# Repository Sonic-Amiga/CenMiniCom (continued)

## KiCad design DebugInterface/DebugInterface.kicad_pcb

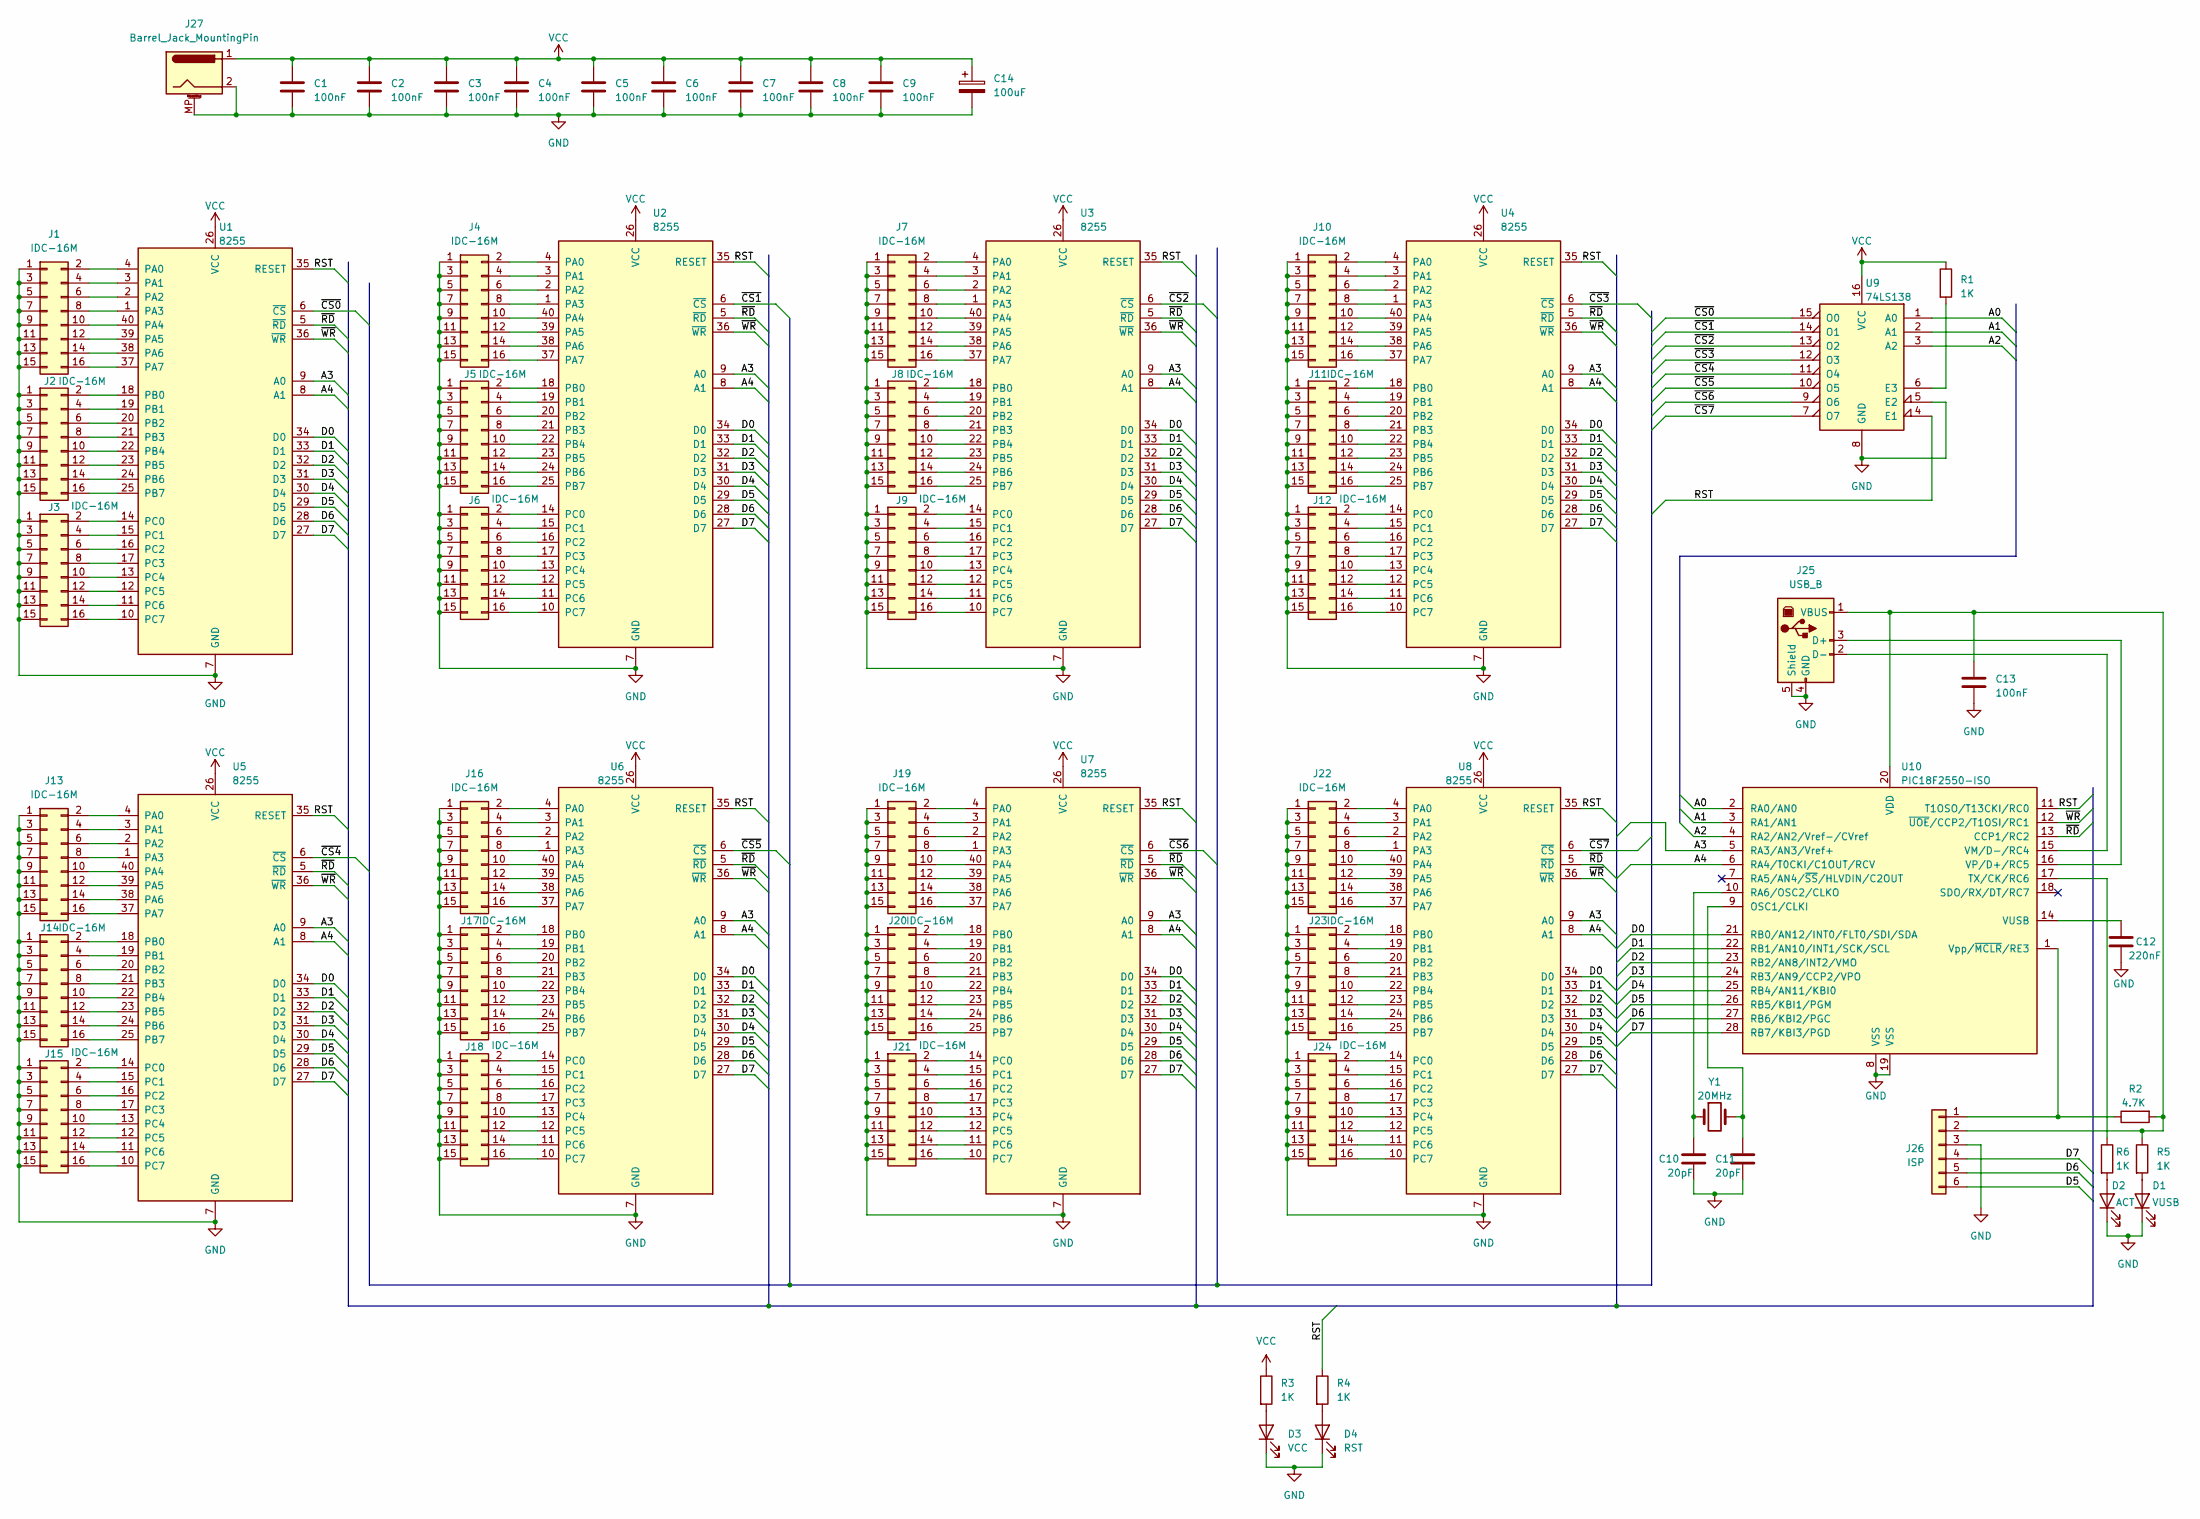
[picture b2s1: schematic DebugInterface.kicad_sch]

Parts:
C1, C2, C3, C4, C5, C6, C7, C8, C9, C13: 100nF; C_Disc_D4.3mm_W1.9mm_P5.00mm
C10, C11: 20pF; C_Disc_D4.3mm_W1.9mm_P5.00mm
C12: 220nF; C_Disc_D4.3mm_W1.9mm_P5.00mm
C14: 100uF; CP_Radial_D8.0mm_P3.80mm
D1: VUSB; LED_D3.0mm
D2: ACT; LED_D3.0mm
D3: VCC; LED_D3.0mm
D4: RST; LED_D3.0mm
J1, J2, J3, J4, J5, J6, J7, J8, J9, J10, J11, J12, J13, J14, J15, J16, J17, J18, J19, J20, J21, J22, J23, J24: IDC-16M; IDC-Header_2x08_P2.54mm_Vertical
J25: USB_B; USB_B_OST_USB-B1HSxx_Horizontal
J26: ISP; PinHeader_1x06_P2.54mm_Vertical
J27: Barrel_Jack_MountingPin; BarrelJack_GCT_DCJ200-10-A_Horizontal
R1, R3, R4, R5, R6: 1K; R_Axial_DIN0207_L6.3mm_D2.5mm_P10.16mm_Horizontal
R2: 4.7K; R_Axial_DIN0207_L6.3mm_D2.5mm_P10.16mm_Horizontal
U1, U2, U3, U4, U5, U6, U7, U8: 8255; DIP-40_W15.24mm
U9: 74LS138; DIP-16_W7.62mm
U10: PIC18F2550-ISO; SOIC-28W_7.5x17.9mm_P1.27mm
Y1: 20MHz; Crystal_HC49-U_Vertical

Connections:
/A0: U9.1 (A0), U10.2 (RA0/AN0)
/A1: U9.2 (A1), U10.3 (RA1/AN1)
/A2: U9.3 (A2), U10.4 (RA2/AN2/Vref-/CVref)
/A3: U1.9 (A0), U2.9 (A0), U3.9 (A0), U4.9 (A0), U5.9 (A0), U6.9 (A0), U7.9 (A0), U8.9 (A0), U10.5 (RA3/AN3/Vref+)
/A4: U1.8 (A1), U2.8 (A1), U3.8 (A1), U4.8 (A1), U5.8 (A1), U6.8 (A1), U7.8 (A1), U8.8 (A1), U10.6 (RA4/T0CKI/C1OUT/RCV)
/D0: U1.34 (D0), U2.34 (D0), U3.34 (D0), U4.34 (D0), U5.34 (D0), U6.34 (D0), U7.34 (D0), U8.34 (D0), U10.21 (RB0/AN12/INT0/FLT0/SDI/SDA)
/D1: U1.33 (D1), U2.33 (D1), U3.33 (D1), U4.33 (D1), U5.33 (D1), U6.33 (D1), U7.33 (D1), U8.33 (D1), U10.22 (RB1/AN10/INT1/SCK/SCL)
/D2: U1.32 (D2), U2.32 (D2), U3.32 (D2), U4.32 (D2), U5.32 (D2), U6.32 (D2), U7.32 (D2), U8.32 (D2), U10.23 (RB2/AN8/INT2/VMO)
/D3: U1.31 (D3), U2.31 (D3), U3.31 (D3), U4.31 (D3), U5.31 (D3), U6.31 (D3), U7.31 (D3), U8.31 (D3), U10.24 (RB3/AN9/CCP2/VPO)
/D4: U1.30 (D4), U2.30 (D4), U3.30 (D4), U4.30 (D4), U5.30 (D4), U6.30 (D4), U7.30 (D4), U8.30 (D4), U10.25 (RB4/AN11/KBI0)
/D5: J26.6, U1.29 (D5), U2.29 (D5), U3.29 (D5), U4.29 (D5), U5.29 (D5), U6.29 (D5), U7.29 (D5), U8.29 (D5), U10.26 (RB5/KBI1/PGM)
/D6: J26.5, U1.28 (D6), U2.28 (D6), U3.28 (D6), U4.28 (D6), U5.28 (D6), U6.28 (D6), U7.28 (D6), U8.28 (D6), U10.27 (RB6/KBI2/PGC)
/D7: J26.4, U1.27 (D7), U2.27 (D7), U3.27 (D7), U4.27 (D7), U5.27 (D7), U6.27 (D7), U7.27 (D7), U8.27 (D7), U10.28 (RB7/KBI3/PGD)
/RST: R4.1, U1.35 (RESET), U2.35 (RESET), U3.35 (RESET), U4.35 (RESET), U5.35 (RESET), U6.35 (RESET), U7.35 (RESET), U8.35 (RESET), U9.4 (E1), U10.11 (T1OSO/T13CKI/RC0)
/~CS0: U1.6 (~CS), U9.15 (O0)
/~CS1: U2.6 (~CS), U9.14 (O1)
/~CS2: U3.6 (~CS), U9.13 (O2)
/~CS3: U4.6 (~CS), U9.12 (O3)
/~CS4: U5.6 (~CS), U9.11 (O4)
/~CS5: U6.6 (~CS), U9.10 (O5)
/~CS6: U7.6 (~CS), U9.9 (O6)
/~CS7: U8.6 (~CS), U9.7 (O7)
/~RD: U1.5 (~RD), U2.5 (~RD), U3.5 (~RD), U4.5 (~RD), U5.5 (~RD), U6.5 (~RD), U7.5 (~RD), U8.5 (~RD), U10.13 (CCP1/RC2)
/~WR: U1.36 (~WR), U2.36 (~WR), U3.36 (~WR), U4.36 (~WR), U5.36 (~WR), U6.36 (~WR), U7.36 (~WR), U8.36 (~WR), U10.12 (~UOE/CCP2/T1OSI/RC1)
GND: C1.2, C2.2, C3.2, C4.2, C5.2, C6.2, C7.2, C8.2, C9.2, C10.1, C11.1, C12.2, C13.2, C14.2, D1.1 (K), D2.1 (K), D3.1 (K), D4.1 (K), J1.1, J1.3, J1.5, J1.7, J1.9, J1.11, J1.13, J1.15, J2.1, J2.3, J2.5, J2.7, J2.9, J2.11, J2.13, J2.15, J3.1, J3.3, J3.5, J3.7, J3.9, J3.11, J3.13, J3.15, J4.1, J4.3, J4.5, J4.7, J4.9, J4.11, J4.13, J4.15, J5.1, J5.3, J5.5, J5.7, J5.9, J5.11, J5.13, J5.15, J6.1, J6.3, J6.5, J6.7, J6.9, J6.11, J6.13, J6.15, J7.1, J7.3, J7.5, J7.7, J7.9, J7.11, J7.13, J7.15, J8.1, J8.3, J8.5, J8.7, J8.9, J8.11, J8.13, J8.15, J9.1, J9.3, J9.5, J9.7, J9.9, J9.11, J9.13, J9.15, J10.1, J10.3, J10.5, J10.7, J10.9, J10.11, J10.13, J10.15, J11.1, J11.3, J11.5, J11.7, J11.9, J11.11, J11.13, J11.15, J12.1, J12.3, J12.5, J12.7, J12.9, J12.11, J12.13, J12.15, J13.1, J13.3, J13.5, J13.7, J13.9, J13.11, J13.13, J13.15, J14.1, J14.3, J14.5, J14.7, J14.9, J14.11, J14.13, J14.15, J15.1, J15.3, J15.5, J15.7, J15.9, J15.11, J15.13, J15.15, J16.1, J16.3, J16.5, J16.7, J16.9, J16.11, J16.13, J16.15, J17.1, J17.3, J17.5, J17.7, J17.9, J17.11, J17.13, J17.15, J18.1, J18.3, J18.5, J18.7, J18.9, J18.11, J18.13, J18.15, J19.1, J19.3, J19.5, J19.7, J19.9, J19.11, J19.13, J19.15, J20.1, J20.3, J20.5, J20.7, J20.9, J20.11, J20.13, J20.15, J21.1, J21.3, J21.5, J21.7, J21.9, J21.11, J21.13, J21.15, J22.1, J22.3, J22.5, J22.7, J22.9, J22.11, J22.13, J22.15, J23.1, J23.3, J23.5, J23.7, J23.9, J23.11, J23.13, J23.15, J24.1, J24.3, J24.5, J24.7, J24.9, J24.11, J24.13, J24.15, J25.4 (GND), J25.5 (Shield), J26.3, J27.2, J27.MP (MountPin), U1.7 (GND), U2.7 (GND), U3.7 (GND), U4.7 (GND), U5.7 (GND), U6.7 (GND), U7.7 (GND), U8.7 (GND), U9.5 (E2), U9.8 (GND), U10.8 (VSS), U10.19 (VSS)
unnamed: D1.2 (A), R5.2
unnamed: D2.2 (A), R6.2
unnamed: D3.2 (A), R3.2
unnamed: D4.2 (A), R4.2
unnamed: J1.2, U1.4 (PA0)
unnamed: J1.4, U1.3 (PA1)
unnamed: J1.6, U1.2 (PA2)
unnamed: J1.8, U1.1 (PA3)
unnamed: J1.10, U1.40 (PA4)
unnamed: J1.12, U1.39 (PA5)
unnamed: J1.14, U1.38 (PA6)
unnamed: J1.16, U1.37 (PA7)
unnamed: J2.2, U1.18 (PB0)
unnamed: J2.4, U1.19 (PB1)
unnamed: J2.6, U1.20 (PB2)
unnamed: J2.8, U1.21 (PB3)
unnamed: J2.10, U1.22 (PB4)
unnamed: J2.12, U1.23 (PB5)
unnamed: J2.14, U1.24 (PB6)
unnamed: J2.16, U1.25 (PB7)
unnamed: J3.2, U1.14 (PC0)
unnamed: J3.4, U1.15 (PC1)
unnamed: J3.6, U1.16 (PC2)
unnamed: J3.8, U1.17 (PC3)
unnamed: J3.10, U1.13 (PC4)
unnamed: J3.12, U1.12 (PC5)
unnamed: J3.14, U1.11 (PC6)
unnamed: J3.16, U1.10 (PC7)
unnamed: J4.2, U2.4 (PA0)
unnamed: J4.4, U2.3 (PA1)
unnamed: J4.6, U2.2 (PA2)
unnamed: J4.8, U2.1 (PA3)
unnamed: J4.10, U2.40 (PA4)
unnamed: J4.12, U2.39 (PA5)
unnamed: J4.14, U2.38 (PA6)
unnamed: J4.16, U2.37 (PA7)
unnamed: J5.2, U2.18 (PB0)
unnamed: J5.4, U2.19 (PB1)
unnamed: J5.6, U2.20 (PB2)
unnamed: J5.8, U2.21 (PB3)
unnamed: J5.10, U2.22 (PB4)
unnamed: J5.12, U2.23 (PB5)
unnamed: J5.14, U2.24 (PB6)
unnamed: J5.16, U2.25 (PB7)
unnamed: J6.2, U2.14 (PC0)
unnamed: J6.4, U2.15 (PC1)
unnamed: J6.6, U2.16 (PC2)
unnamed: J6.8, U2.17 (PC3)
unnamed: J6.10, U2.13 (PC4)
unnamed: J6.12, U2.12 (PC5)
unnamed: J6.14, U2.11 (PC6)
unnamed: J6.16, U2.10 (PC7)
unnamed: J7.2, U3.4 (PA0)
unnamed: J7.4, U3.3 (PA1)
unnamed: J7.6, U3.2 (PA2)
unnamed: J7.8, U3.1 (PA3)
unnamed: J7.10, U3.40 (PA4)
unnamed: J7.12, U3.39 (PA5)
unnamed: J7.14, U3.38 (PA6)
unnamed: J7.16, U3.37 (PA7)
unnamed: J8.2, U3.18 (PB0)
unnamed: J8.4, U3.19 (PB1)
unnamed: J8.6, U3.20 (PB2)
unnamed: J8.8, U3.21 (PB3)
unnamed: J8.10, U3.22 (PB4)
unnamed: J8.12, U3.23 (PB5)
unnamed: J8.14, U3.24 (PB6)
unnamed: J8.16, U3.25 (PB7)
unnamed: J9.2, U3.14 (PC0)
unnamed: J9.4, U3.15 (PC1)
unnamed: J9.6, U3.16 (PC2)
unnamed: J9.8, U3.17 (PC3)
unnamed: J9.10, U3.13 (PC4)
unnamed: J9.12, U3.12 (PC5)
unnamed: J9.14, U3.11 (PC6)
unnamed: J9.16, U3.10 (PC7)
unnamed: J10.2, U4.4 (PA0)
unnamed: J10.4, U4.3 (PA1)
unnamed: J10.6, U4.2 (PA2)
unnamed: J10.8, U4.1 (PA3)
unnamed: J10.10, U4.40 (PA4)
unnamed: J10.12, U4.39 (PA5)
unnamed: J10.14, U4.38 (PA6)
unnamed: J10.16, U4.37 (PA7)
unnamed: J11.2, U4.18 (PB0)
unnamed: J11.4, U4.19 (PB1)
unnamed: J11.6, U4.20 (PB2)
unnamed: J11.8, U4.21 (PB3)
unnamed: J11.10, U4.22 (PB4)
unnamed: J11.12, U4.23 (PB5)
unnamed: J11.14, U4.24 (PB6)
unnamed: J11.16, U4.25 (PB7)
unnamed: J12.2, U4.14 (PC0)
unnamed: J12.4, U4.15 (PC1)
unnamed: J12.6, U4.16 (PC2)
unnamed: J12.8, U4.17 (PC3)
unnamed: J12.10, U4.13 (PC4)
unnamed: J12.12, U4.12 (PC5)
unnamed: J12.14, U4.11 (PC6)
unnamed: J12.16, U4.10 (PC7)
unnamed: J13.2, U5.4 (PA0)
unnamed: J13.4, U5.3 (PA1)
unnamed: J13.6, U5.2 (PA2)
unnamed: J13.8, U5.1 (PA3)
unnamed: J13.10, U5.40 (PA4)
unnamed: J13.12, U5.39 (PA5)
unnamed: J13.14, U5.38 (PA6)
unnamed: J13.16, U5.37 (PA7)
unnamed: J14.2, U5.18 (PB0)
unnamed: J14.4, U5.19 (PB1)
unnamed: J14.6, U5.20 (PB2)
unnamed: J14.8, U5.21 (PB3)
unnamed: J14.10, U5.22 (PB4)
unnamed: J14.12, U5.23 (PB5)
unnamed: J14.14, U5.24 (PB6)
unnamed: J14.16, U5.25 (PB7)
unnamed: J15.2, U5.14 (PC0)
unnamed: J15.4, U5.15 (PC1)
unnamed: J15.6, U5.16 (PC2)
unnamed: J15.8, U5.17 (PC3)
unnamed: J15.10, U5.13 (PC4)
unnamed: J15.12, U5.12 (PC5)
unnamed: J15.14, U5.11 (PC6)
unnamed: J15.16, U5.10 (PC7)
unnamed: J16.2, U6.4 (PA0)
unnamed: J16.4, U6.3 (PA1)
unnamed: J16.6, U6.2 (PA2)
unnamed: J16.8, U6.1 (PA3)
unnamed: J16.10, U6.40 (PA4)
unnamed: J16.12, U6.39 (PA5)
unnamed: J16.14, U6.38 (PA6)
unnamed: J16.16, U6.37 (PA7)
unnamed: J17.2, U6.18 (PB0)
unnamed: J17.4, U6.19 (PB1)
unnamed: J17.6, U6.20 (PB2)
unnamed: J17.8, U6.21 (PB3)
unnamed: J17.10, U6.22 (PB4)
unnamed: J17.12, U6.23 (PB5)
unnamed: J17.14, U6.24 (PB6)
unnamed: J17.16, U6.25 (PB7)
unnamed: J18.2, U6.14 (PC0)
unnamed: J18.4, U6.15 (PC1)
unnamed: J18.6, U6.16 (PC2)
unnamed: J18.8, U6.17 (PC3)
unnamed: J18.10, U6.13 (PC4)
unnamed: J18.12, U6.12 (PC5)
unnamed: J18.14, U6.11 (PC6)
unnamed: J18.16, U6.10 (PC7)
unnamed: J19.2, U7.4 (PA0)
unnamed: J19.4, U7.3 (PA1)
unnamed: J19.6, U7.2 (PA2)
unnamed: J19.8, U7.1 (PA3)
unnamed: J19.10, U7.40 (PA4)
unnamed: J19.12, U7.39 (PA5)
unnamed: J19.14, U7.38 (PA6)
unnamed: J19.16, U7.37 (PA7)
unnamed: J20.2, U7.18 (PB0)
unnamed: J20.4, U7.19 (PB1)
unnamed: J20.6, U7.20 (PB2)
unnamed: J20.8, U7.21 (PB3)
unnamed: J20.10, U7.22 (PB4)
unnamed: J20.12, U7.23 (PB5)
unnamed: J20.14, U7.24 (PB6)
unnamed: J20.16, U7.25 (PB7)
unnamed: J21.2, U7.14 (PC0)
unnamed: J21.4, U7.15 (PC1)
unnamed: J21.6, U7.16 (PC2)
unnamed: J21.8, U7.17 (PC3)
unnamed: J21.10, U7.13 (PC4)
unnamed: J21.12, U7.12 (PC5)
unnamed: J21.14, U7.11 (PC6)
unnamed: J21.16, U7.10 (PC7)
unnamed: J22.2, U8.4 (PA0)
unnamed: J22.4, U8.3 (PA1)
unnamed: J22.6, U8.2 (PA2)
unnamed: J22.8, U8.1 (PA3)
unnamed: J22.10, U8.40 (PA4)
unnamed: J22.12, U8.39 (PA5)
unnamed: J22.14, U8.38 (PA6)
unnamed: J22.16, U8.37 (PA7)
unnamed: J23.2, U8.18 (PB0)
unnamed: J23.4, U8.19 (PB1)
unnamed: J23.6, U8.20 (PB2)
unnamed: J23.8, U8.21 (PB3)
unnamed: J23.10, U8.22 (PB4)
unnamed: J23.12, U8.23 (PB5)
unnamed: J23.14, U8.24 (PB6)
unnamed: J23.16, U8.25 (PB7)
unnamed: J24.2, U8.14 (PC0)
unnamed: J24.4, U8.15 (PC1)
unnamed: J24.6, U8.16 (PC2)
unnamed: J24.8, U8.17 (PC3)
unnamed: J24.10, U8.13 (PC4)
unnamed: J24.12, U8.12 (PC5)
unnamed: J24.14, U8.11 (PC6)
unnamed: J24.16, U8.10 (PC7)
unnamed: J25.3 (D+), U10.16 (VP/D+/RC5)
unnamed: J25.2 (D-), U10.15 (VM/D-/RC4)
unnamed: C13.1, J25.1 (VBUS), J26.2, R2.2, R5.1, U10.20 (VDD)
unnamed: J26.1, R2.1, U10.1 (Vpp/~MCLR/RE3)
unnamed: R1.2, U9.6 (E3)
unnamed: C11.2, U10.9 (OSC1/CLKI), Y1.2
unnamed: C10.2, U10.10 (RA6/OSC2/CLKO), Y1.1
unnamed: R6.1, U10.17 (TX/CK/RC6)
unnamed: C12.1, U10.14 (VUSB)
VCC: C1.1, C2.1, C3.1, C4.1, C5.1, C6.1, C7.1, C8.1, C9.1, C14.1, J27.1, R1.1, R3.1, U1.26 (VCC), U2.26 (VCC), U3.26 (VCC), U4.26 (VCC), U5.26 (VCC), U6.26 (VCC), U7.26 (VCC), U8.26 (VCC), U9.16 (VCC)

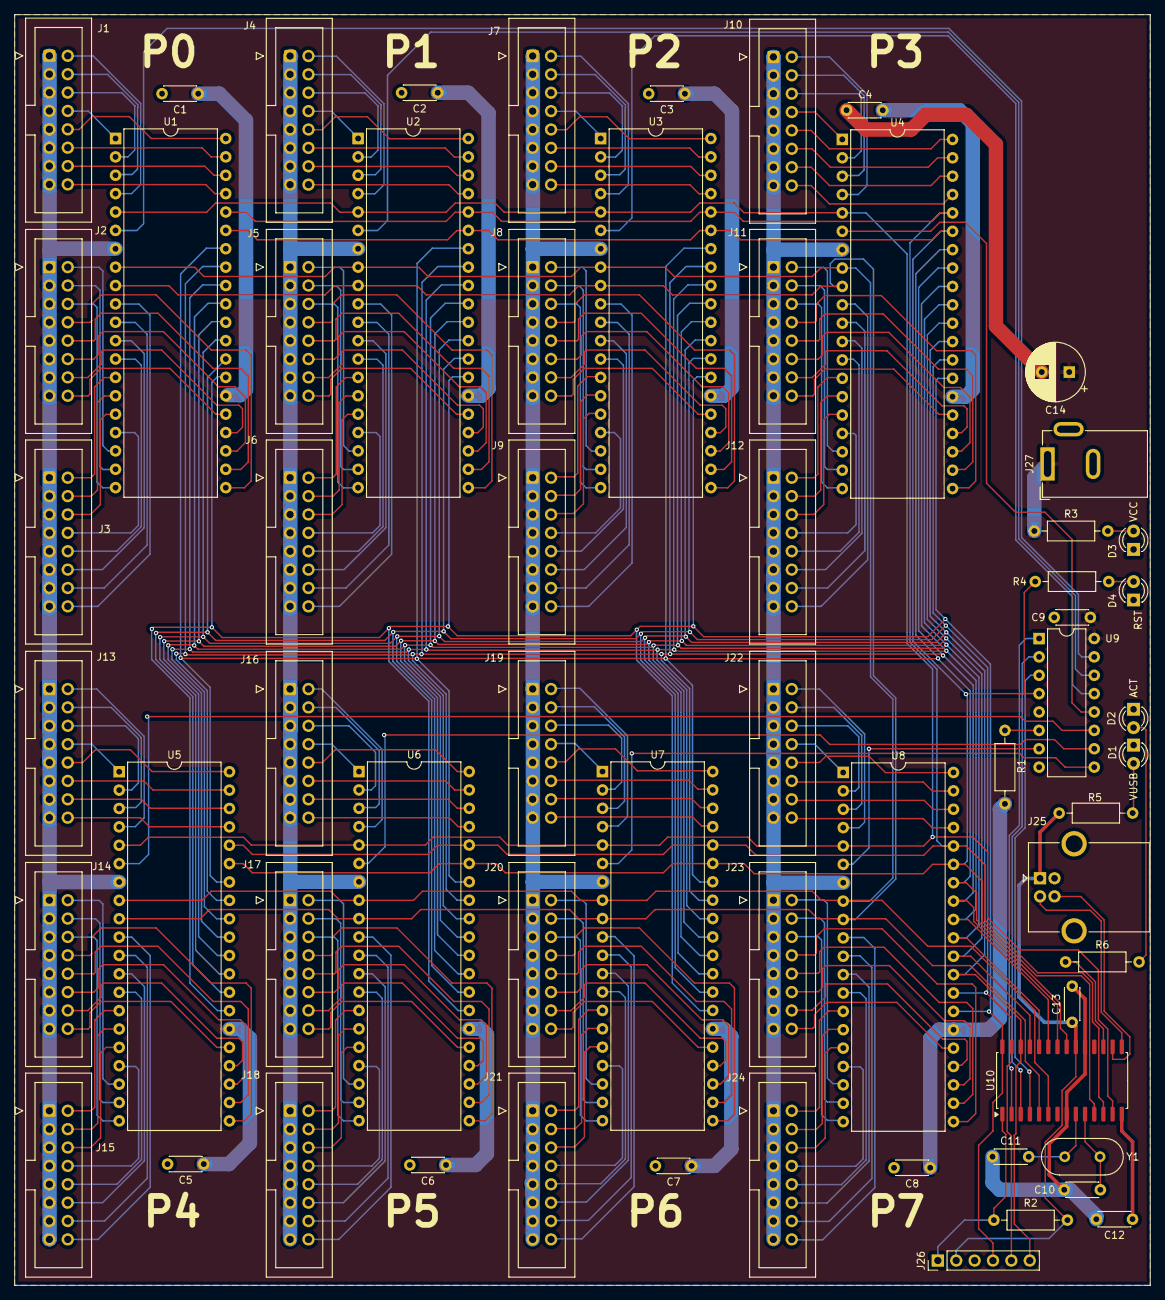
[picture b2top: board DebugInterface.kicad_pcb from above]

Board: 2 copper layers, 157.0 x 175.6 mm, 62 parts (0 on the bottom side), 231 nets.

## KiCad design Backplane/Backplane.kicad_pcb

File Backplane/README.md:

# Backplane board replica

# Modifications list.

1. TBP18S42N ROM is a complete ubobtanium, so i found a russian КР556РТ5 (KR556RT5)
one-time fuse ROM. A cross-reference site gave "3605" as a western analog for the
chip, so let it be so.

2. PCB-mounted edge slots are also a complete unobtanium here, i only found ones for
soldering wires, they are called SLM-72:
https://www.arcadepartsandrepair.com/store/pinball-kits-parts/pinball-parts/72-pin-edge-connector-w-solder-eyelet-leads-ec1007/
Therefore this PCB is a shortened version, only containing boot ROM and LED buffers, but
the design is modular and can be extended, see assembly notes.
Connection to the bus is made using a 50-pin connector, you may use IDC type with a flat
ribbon cable. 
If you have access to the PCB-mounted connectors, please feel free to extend the project.
I will be happy to host the full version in the repository.

3. Real-time clock reference generator has been omitted. Modern PSUs don't output any low
voltage AC, and it's much easier to just generate the frequency needed. Since the signal
comes into the CPU from front panel side, front panel board takes care of it.

Russian characters in this file are using UTF-8 character set.

# Assembly notes

Possible chip replacements:

|Original       |Replacement            |
|---------------|-----------------------|
|3604		|К556РТ5		|
|7425		|155ЛЕ3			|
|74LS04         |К555ЛН1		|
|74LS20		|К555ЛА1		|
|74LS38		|К555ЛА13		|

As noticed above, this backplane design is modular, and can be used with both wired and PCB backplane
design. For the purpose, the J2 connector is designed as a horisontal 2x25 pins row. It is possible
to attach a second board, containing edge slots, directly to it, thus producing a full-sized backplane.
Alternatively, an IDC-50 connector can be installed with a flat ribbon cable, going to a wired backplane
(this will be my implementation). Sorry, due to a lack of time i don't have a design for the second PCB,
but i would be happy if someone contributes.

# Revision history.

28.11.2022 - rev 1.0

* Erratum E001: Incorrect DIP chip width is used for 3604

# Contacts

Please direct all questions to pavel_fedin@mail.ru

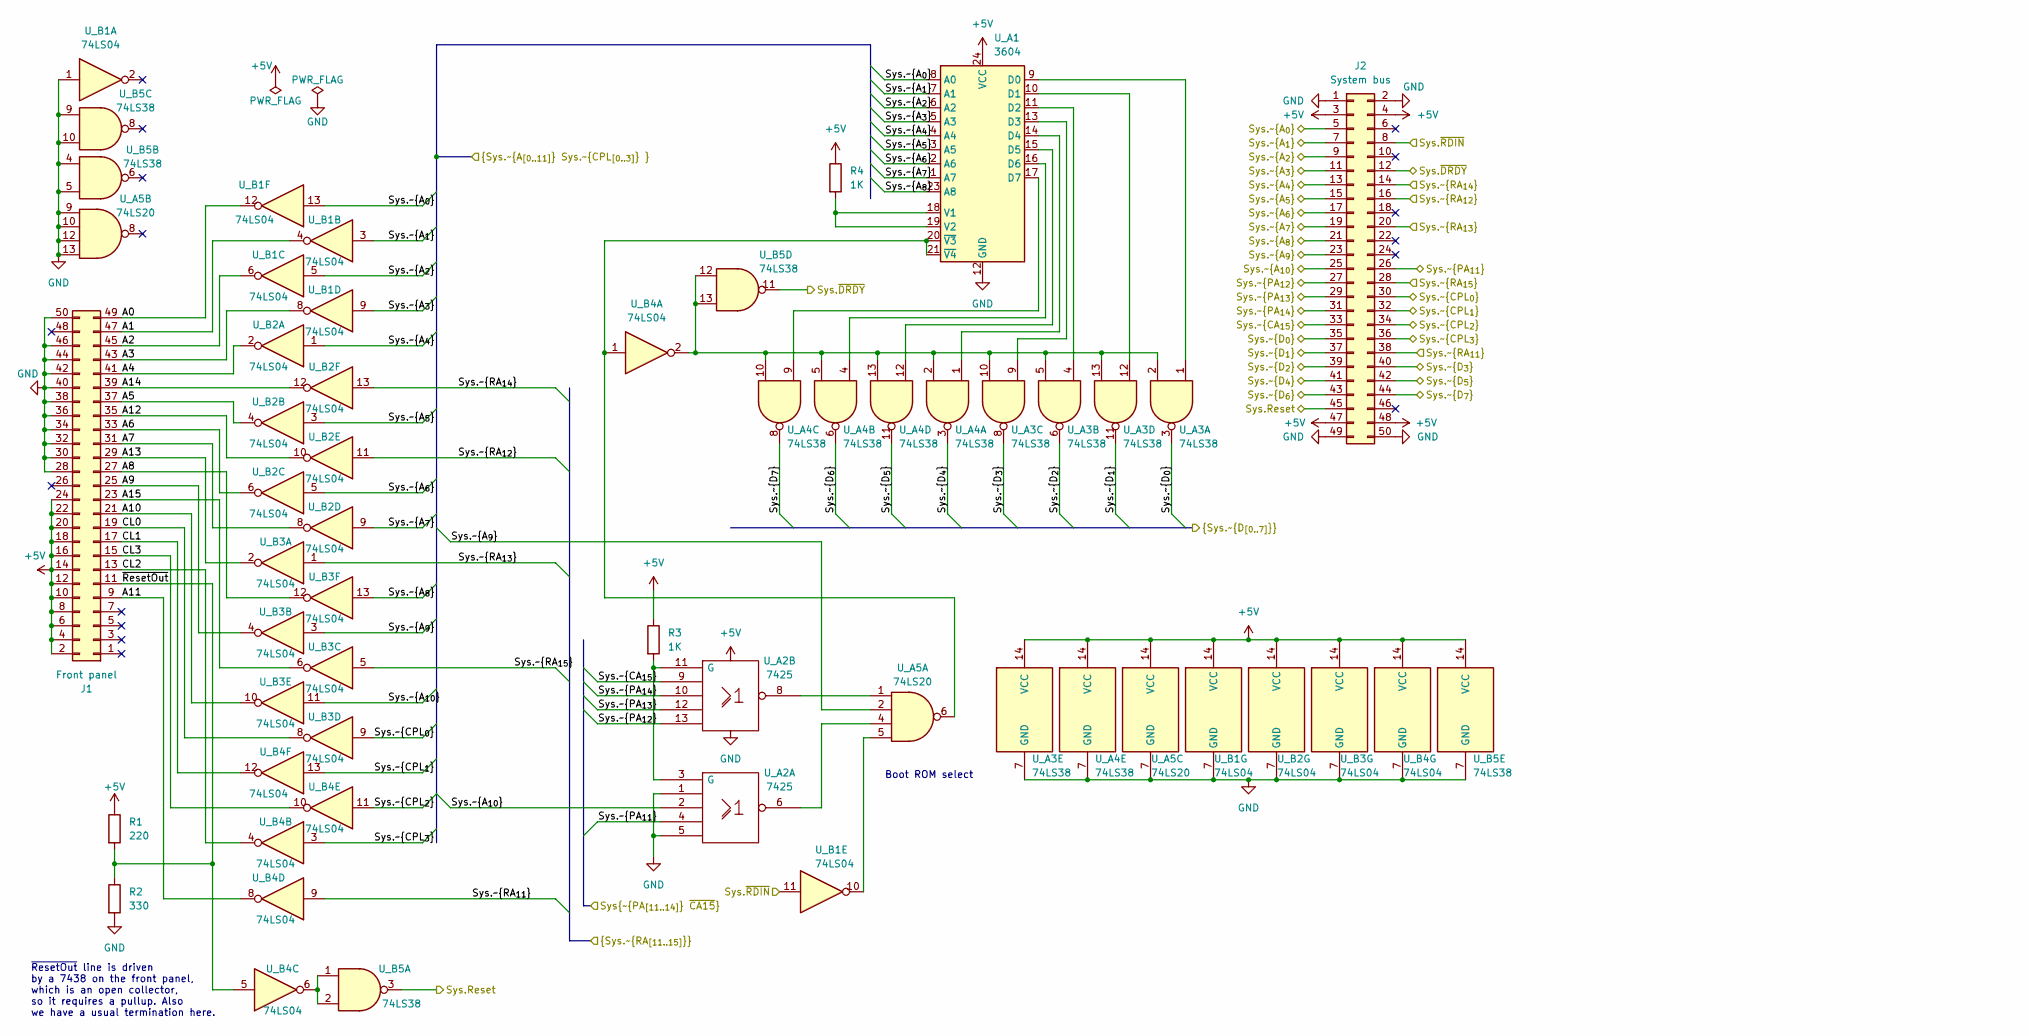
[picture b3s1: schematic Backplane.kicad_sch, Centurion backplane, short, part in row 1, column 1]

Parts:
J1: Front panel; IDC-Header_2x25_P2.54mm_Vertical
J2: System bus; PinHeader_2x25_P2.54mm_Horizontal
R1: 220; R_Axial_DIN0207_L6.3mm_D2.5mm_P10.16mm_Horizontal
R2: 330; R_Axial_DIN0207_L6.3mm_D2.5mm_P10.16mm_Horizontal
R3, R4: 1K; R_Axial_DIN0207_L6.3mm_D2.5mm_P10.16mm_Horizontal
U_A1: 3604; DIP-24_W15.24mm_Socket
U_A2: 7425; DIP-14_W7.62mm
U_A3, U_A4: 74LS38; DIP-14_W7.62mm
U_A5: 74LS20; DIP-14_W7.62mm
U_B1, U_B2, U_B3, U_B4: 74LS04; DIP-14_W7.62mm
U_B5: 74LS38; DIP-14_W7.62mm

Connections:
+5V: J1.2, J1.4, J1.6, J1.8, J1.10, J1.12, J1.14, J1.16, J1.18, J1.20, J1.22, J1.24, J2.3, J2.4, J2.47, J2.48, R1.1, R3.1, R4.1, U_A1.24 (VCC), U_A2.14 (Vcc), U_A3.14 (VCC), U_A4.14 (VCC), U_A5.14 (VCC), U_B1.14 (VCC), U_B2.14 (VCC), U_B3.14 (VCC), U_B4.14 (VCC), U_B5.14 (VCC)
/A0: J1.49, U_B1.12
/A1: J1.47, U_B1.4
/A2: J1.45, U_B1.6
/A3: J1.43, U_B1.8
/A4: J1.41, U_B2.2
/A5: J1.37, U_B2.4
/A6: J1.33, U_B2.6
/A7: J1.31, U_B2.8
/A8: J1.27, U_B3.12
/A9: J1.25, U_B3.4
/A10: J1.21, U_B3.10
/A11: J1.9, U_B4.8
/A12: J1.35, U_B2.10
/A13: J1.29, U_B3.2
/A14: J1.39, U_B2.12
/A15: J1.23, U_B3.6
/CL0: J1.19, U_B3.8
/CL1: J1.17, U_B4.12
/CL2: J1.13, U_B4.4
/CL3: J1.15, U_B4.10
/Sys.Reset: J2.45, U_B5.3
/Sys.~A_{0}: J2.5, U_A1.8 (A0), U_B1.13
/Sys.~A_{1}: J2.7, U_A1.7 (A1), U_B1.3
/Sys.~A_{2}: J2.9, U_A1.6 (A2), U_B1.5
/Sys.~A_{3}: J2.11, U_A1.5 (A3), U_B1.9
/Sys.~A_{4}: J2.13, U_A1.4 (A4), U_B2.1
/Sys.~A_{5}: J2.15, U_A1.3 (A5), U_B2.3
/Sys.~A_{6}: J2.17, U_A1.2 (A6), U_B2.5
/Sys.~A_{7}: J2.19, U_A1.1 (A7), U_B2.9
/Sys.~A_{8}: J2.21, U_A1.23 (A8), U_B3.13
/Sys.~A_{9}: J2.23, U_A5.2, U_B3.3
/Sys.~A_{10}: J2.25, U_A2.2, U_B3.11
/Sys.~CA_{15}: J2.33, U_A2.9
/Sys.~CPL_{0}: J2.30, U_B3.9
/Sys.~CPL_{1}: J2.32, U_B4.13
/Sys.~CPL_{2}: J2.34, U_B4.11
/Sys.~CPL_{3}: J2.36, U_B4.3
/Sys.~DRDY: J2.12, U_B5.11
/Sys.~D_{0}: J2.35, U_A3.3
/Sys.~D_{1}: J2.37, U_A3.11
/Sys.~D_{2}: J2.39, U_A3.6
/Sys.~D_{3}: J2.40, U_A3.8
/Sys.~D_{4}: J2.41, U_A4.3
/Sys.~D_{5}: J2.42, U_A4.11
/Sys.~D_{6}: J2.43, U_A4.6
/Sys.~D_{7}: J2.44, U_A4.8
/Sys.~PA_{11}: J2.26, U_A2.4
/Sys.~PA_{12}: J2.27, U_A2.13
/Sys.~PA_{13}: J2.29, U_A2.12
/Sys.~PA_{14}: J2.31, U_A2.10
/Sys.~RA_{11}: J2.38, U_B4.9
/Sys.~RA_{12}: J2.16, U_B2.11
/Sys.~RA_{13}: J2.20, U_B3.1
/Sys.~RA_{14}: J2.14, U_B2.13
/Sys.~RA_{15}: J2.28, U_B3.5
/Sys.~RDIN: J2.8, U_B1.11
/~ResetOut: J1.11, R1.2, R2.1, U_B4.5
GND: J1.28, J1.30, J1.32, J1.34, J1.36, J1.38, J1.40, J1.42, J1.44, J1.46, J1.50, J2.1, J2.2, J2.49, J2.50, R2.2, U_A1.12 (GND), U_A2.1, U_A2.5, U_A2.7 (Gnd), U_A3.7 (GND), U_A4.7 (GND), U_A5.7 (GND), U_A5.9, U_A5.10, U_A5.12, U_A5.13, U_B1.1, U_B1.7 (GND), U_B2.7 (GND), U_B3.7 (GND), U_B4.7 (GND), U_B5.4, U_B5.5, U_B5.7 (GND), U_B5.9, U_B5.10
unnamed: R3.2, U_A2.3 (G), U_A2.11 (G)
unnamed: R4.2, U_A1.18 (V1), U_A1.19 (V2)
unnamed: U_A1.9 (D0), U_A3.1
unnamed: U_A1.10 (D1), U_A3.12
unnamed: U_A1.11 (D2), U_A3.4
unnamed: U_A1.13 (D3), U_A3.9
unnamed: U_A1.14 (D4), U_A4.1
unnamed: U_A1.15 (D5), U_A4.12
unnamed: U_A1.16 (D6), U_A4.4
unnamed: U_A1.17 (D7), U_A4.9
unnamed: U_A1.20 (~V3), U_A1.21 (~V4), U_A5.6, U_B4.1
unnamed: U_A2.6, U_A5.4
unnamed: U_A2.8, U_A5.1
unnamed: U_A3.2, U_A3.5, U_A3.10, U_A3.13, U_A4.2, U_A4.5, U_A4.10, U_A4.13, U_B4.2, U_B5.12, U_B5.13
unnamed: U_A5.5, U_B1.10
unnamed: U_B4.6, U_B5.1, U_B5.2

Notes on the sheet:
Boot ROM select
~{ResetOut} line is driven by a 7438 on the front panel, which is an open collector, so it requires a pullup. Also we have a usual termination here.

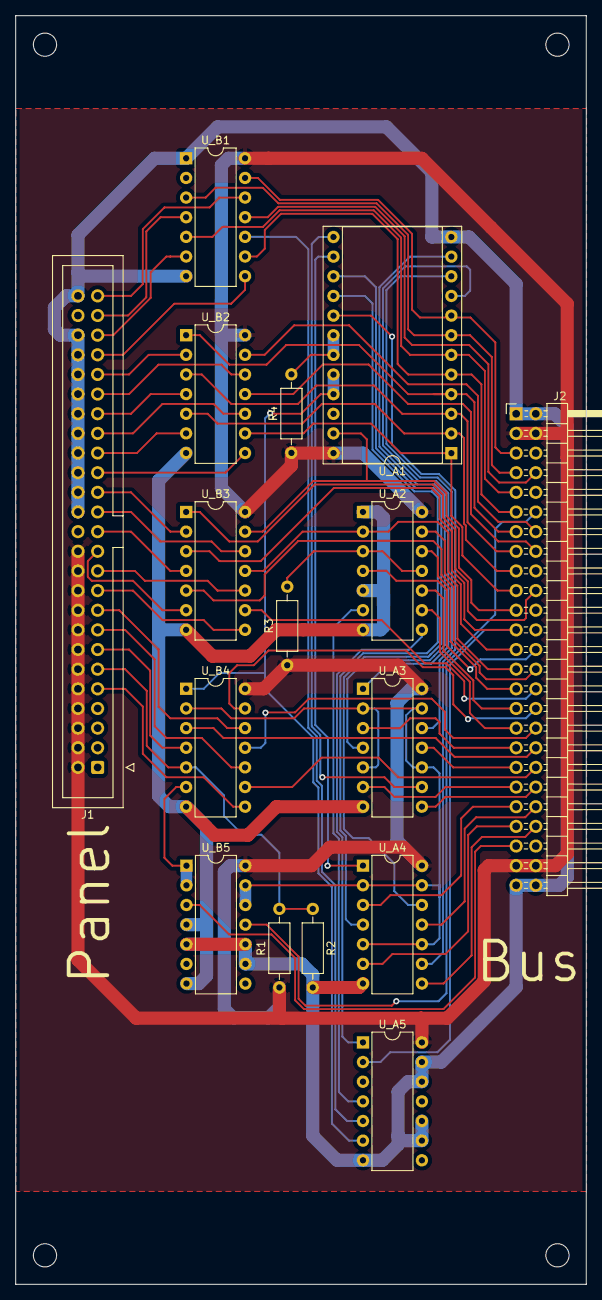
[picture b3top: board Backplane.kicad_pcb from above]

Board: 2 copper layers, 73.8 x 164.0 mm, 16 parts (0 on the bottom side), 75 nets.
